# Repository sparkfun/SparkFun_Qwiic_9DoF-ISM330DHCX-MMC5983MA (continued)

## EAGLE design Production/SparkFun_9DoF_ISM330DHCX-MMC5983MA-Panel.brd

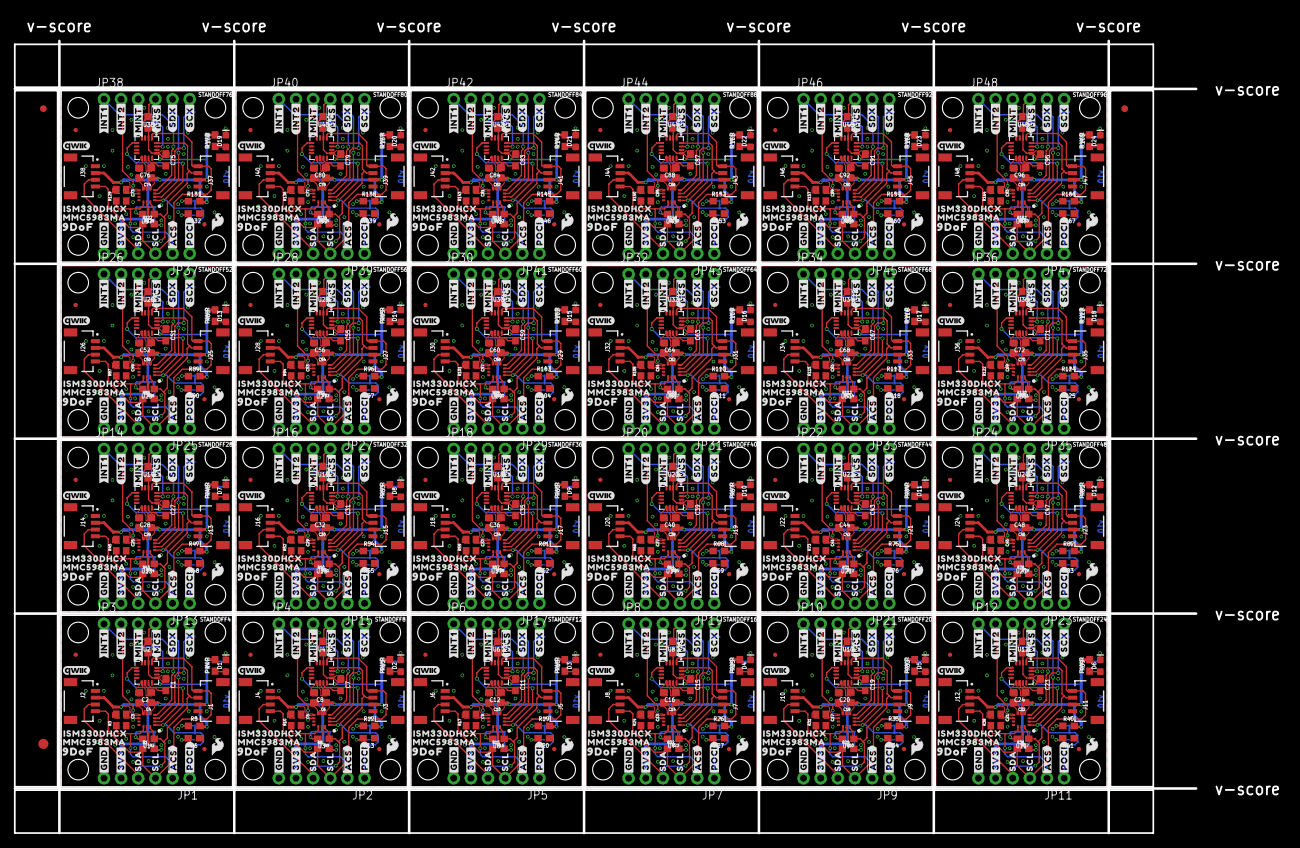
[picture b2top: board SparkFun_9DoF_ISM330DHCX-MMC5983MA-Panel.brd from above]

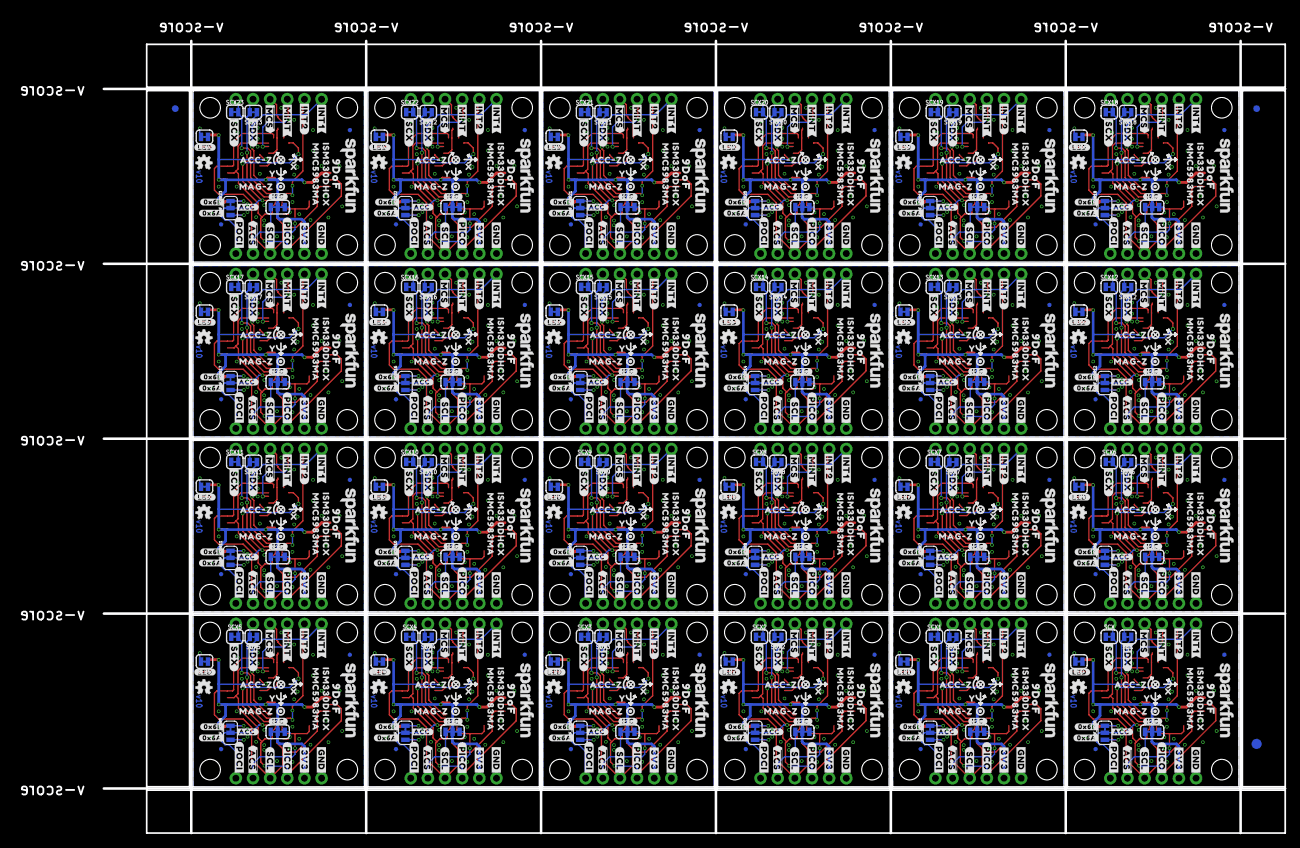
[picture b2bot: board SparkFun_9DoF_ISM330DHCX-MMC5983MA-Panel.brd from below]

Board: 2 copper layers, 175.0 x 117.3 mm, 1806 parts (795 on the bottom side), 456 nets.

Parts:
6DOF_ADDR, 6DOF_ADDR1, 6DOF_ADDR2, 6DOF_ADDR3, 6DOF_ADDR4, 6DOF_ADDR5, 6DOF_ADDR6, 6DOF_ADDR7, 6DOF_ADDR8, 6DOF_ADDR9, 6DOF_ADDR10, 6DOF_ADDR11, 6DOF_ADDR12, 6DOF_ADDR13, 6DOF_ADDR14, 6DOF_ADDR15, 6DOF_ADDR16, 6DOF_ADDR17, 6DOF_ADDR18, 6DOF_ADDR19, 6DOF_ADDR20, 6DOF_ADDR21, 6DOF_ADDR22, 6DOF_ADDR23: JUMPER-SMT_3_1-NC_TRACE_SILK; SMT-JUMPER_3_1-NC_TRACE_SILK
C1, C7, C11, C15, C19, C23, C27, C31, C35, C39, C43, C47, C51, C55, C59, C63, C67, C71, C75, C79, C83, C87, C91, C95: 1.0uF; 0603
C2, C8, C12, C16, C20, C24, C28, C32, C36, C40, C44, C48, C52, C56, C60, C64, C68, C72, C76, C80, C84, C88, C92, C96: 10uF; 0603
C3, C4, C5, C6, C9, C10, C13, C14, C17, C18, C21, C22, C25, C26, C29, C30, C33, C34, C37, C38, C41, C42, C45, C46, C49, C50, C53, C54, C57, C58, C61, C62, C65, C66, C69, C70, C73, C74, C77, C78, C81, C82, C85, C86, C89, C90, C93, C94: 0.1uF; 0603
D1, D2, D3, D4, D5, D6, D7, D8, D9, D10, D11, D12, D13, D14, D15, D16, D17, D18, D19, D20, D21, D22, D23, D24: RED; LED-0603
E$1, E$2, E$3, E$4: FIDUCIAL-1X2
E$5, E$6: FIDUCIAL-1.5X3
FD1, FD2, FD3, FD4, FD5, FD6, FD7, FD8, FD9, FD10, FD11, FD12, FD13, FD14, FD15, FD16, FD17, FD18, FD19, FD20, FD21, FD22, FD23, FD24, FD25, FD26, FD27, FD28, FD29, FD30, FD31, FD32, FD33, FD34, FD35, FD36, FD37, FD38, FD39, FD40, FD41, FD42, FD43, FD44, FD45, FD46, FD47, FD48: FIDUCIALUFIDUCIAL; FIDUCIAL-MICRO
FID1, FID2, FID3, FID4, FID5, FID6, FID7, FID8, FID9, FID10, FID11, FID12, FID13, FID14, FID15, FID16, FID17, FID18, FID19, FID20, FID21, FID22, FID23, FID24, FID25, FID26, FID27, FID28, FID29, FID30, FID31, FID32, FID33, FID34, FID35, FID36, FID37, FID38, FID39, FID40, FID41, FID42, FID43, FID44, FID45, FID46, FID47, FID48: FIDUCIALUFIDUCIAL; FIDUCIAL-MICRO
I2C_PU, I2C_PU1, I2C_PU2, I2C_PU3, I2C_PU4, I2C_PU5, I2C_PU6, I2C_PU7, I2C_PU8, I2C_PU9, I2C_PU10, I2C_PU11, I2C_PU12, I2C_PU13, I2C_PU14, I2C_PU15, I2C_PU16, I2C_PU17, I2C_PU18, I2C_PU19, I2C_PU20, I2C_PU21, I2C_PU22, I2C_PU23: S_MODE; SMT-JUMPER_3_2-NC_TRACE_SILK
J1, J2, J3, J4, J5, J6, J7, J8, J9, J10, J11, J12, J13, J14, J15, J16, J17, J18, J19, J20, J21, J22, J23, J24, J25, J26, J27, J28, J29, J30, J31, J32, J33, J34, J35, J36, J37, J38, J39, J40, J41, J42, J43, J44, J45, J46, J47, J48: QWIIC_RIGHT_ANGLE; JST04_1MM_RA
JP1, JP2, JP3, JP4, JP5, JP6, JP7, JP8, JP9, JP10, JP11, JP12, JP13, JP14, JP15, JP16, JP17, JP18, JP19, JP20, JP21, JP22, JP23, JP24, JP25, JP26, JP27, JP28, JP29, JP30, JP31, JP32, JP33, JP34, JP35, JP36, JP37, JP38, JP39, JP40, JP41, JP42, JP43, JP44, JP45, JP46, JP47, JP48: IO; 1X06_NO_SILK
LED, LED1, LED2, LED3, LED4, LED5, LED6, LED7, LED8, LED9, LED10, LED11, LED12, LED13, LED14, LED15, LED16, LED17, LED18, LED19, LED20, LED21, LED22, LED23: JUMPER-SMT_2_NC_TRACE_SILK; SMT-JUMPER_2_NC_TRACE_SILK
LOGO1, LOGO6, LOGO9, LOGO12, LOGO15, LOGO18, LOGO21, LOGO24, LOGO27, LOGO30, LOGO33, LOGO36, LOGO39, LOGO42, LOGO45, LOGO48, LOGO51, LOGO54, LOGO57, LOGO60, LOGO63, LOGO66, LOGO69, LOGO72: QWIIC_LOGO_4MM; QWIIC_4MM
LOGO2, LOGO4, LOGO7, LOGO10, LOGO13, LOGO16, LOGO19, LOGO22, LOGO25, LOGO28, LOGO31, LOGO34, LOGO37, LOGO40, LOGO43, LOGO46, LOGO49, LOGO52, LOGO55, LOGO58, LOGO61, LOGO64, LOGO67, LOGO70: OSHW-LOGOMINI; OSHW-LOGO-MINI
LOGO3, LOGO5, LOGO8, LOGO11, LOGO14, LOGO17, LOGO20, LOGO23, LOGO26, LOGO29, LOGO32, LOGO35, LOGO38, LOGO41, LOGO44, LOGO47, LOGO50, LOGO53, LOGO56, LOGO59, LOGO62, LOGO65, LOGO68, LOGO71: SFE_LOGO_NAME.1_INCH; SFE_LOGO_NAME_.1
R1, R2, R8, R9, R15, R16, R22, R23, R29, R30, R36, R37, R43, R44, R50, R51, R57, R58, R64, R65, R71, R72, R78, R79, R85, R86, R92, R93, R99, R100, R106, R107, R113, R114, R120, R121, R127, R128, R134, R135, R141, R142, R148, R149, R155, R156, R162, R163: 2.2k; 0603
R3, R5, R6, R7, R10, R12, R13, R14, R17, R19, R20, R21, R24, R26, R27, R28, R31, R33, R34, R35, R38, R40, R41, R42, R45, R47, R48, R49, R52, R54, R55, R56, R59, R61, R62, R63, R66, R68, R69, R70, R73, R75, R76, R77, R80, R82, R83, R84, R87, R89, R90, R91, R94, R96, R97, R98, R101, R103, R104, R105, R108, R110, R111, R112, R115, R117, R118, R119, R122, R124, R125, R126, R129, R131, R132, R133, R136, R138, R139, R140, R143, R145, R146, R147, R150, R152, R153, R154, R157, R159, R160, R161, R164, R166, R167, R168: 100k; 0603
R4, R11, R18, R25, R32, R39, R46, R53, R60, R67, R74, R81, R88, R95, R102, R109, R116, R123, R130, R137, R144, R151, R158, R165: 1k; 0603
SCX, SCX1, SCX2, SCX3, SCX4, SCX5, SCX6, SCX7, SCX8, SCX9, SCX10, SCX11, SCX12, SCX13, SCX14, SCX15, SCX16, SCX17, SCX18, SCX19, SCX20, SCX21, SCX22, SCX23: JUMPER-SMT_2_NC_TRACE_SILK; SMT-JUMPER_2_NC_TRACE_SILK
SDX, SDX1, SDX2, SDX3, SDX4, SDX5, SDX6, SDX7, SDX8, SDX9, SDX10, SDX11, SDX12, SDX13, SDX14, SDX15, SDX16, SDX17, SDX18, SDX19, SDX20, SDX21, SDX22, SDX23: JUMPER-SMT_2_NC_TRACE_SILK; SMT-JUMPER_2_NC_TRACE_SILK
STANDOFF1, STANDOFF2, STANDOFF3, STANDOFF4, STANDOFF5, STANDOFF6, STANDOFF7, STANDOFF8, STANDOFF9, STANDOFF10, STANDOFF11, STANDOFF12, STANDOFF13, STANDOFF14, STANDOFF15, STANDOFF16, STANDOFF17, STANDOFF18, STANDOFF19, STANDOFF20, STANDOFF21, STANDOFF22, STANDOFF23, STANDOFF24, STANDOFF25, STANDOFF26, STANDOFF27, STANDOFF28, STANDOFF29, STANDOFF30, STANDOFF31, STANDOFF32, STANDOFF33, STANDOFF34, STANDOFF35, STANDOFF36, STANDOFF37, STANDOFF38, STANDOFF39, STANDOFF40, STANDOFF41, STANDOFF42, STANDOFF43, STANDOFF44, STANDOFF45, STANDOFF46, STANDOFF47, STANDOFF48, STANDOFF49, STANDOFF50, STANDOFF51, STANDOFF52, STANDOFF53, STANDOFF54, STANDOFF55, STANDOFF56, STANDOFF57, STANDOFF58, STANDOFF59, STANDOFF60, STANDOFF61, STANDOFF62, STANDOFF63, STANDOFF64, STANDOFF65, STANDOFF66, STANDOFF67, STANDOFF68, STANDOFF69, STANDOFF70, STANDOFF71, STANDOFF72, STANDOFF73, STANDOFF74, STANDOFF75, STANDOFF76, STANDOFF77, STANDOFF78, STANDOFF79, STANDOFF80, STANDOFF81, STANDOFF82, STANDOFF83, STANDOFF84, STANDOFF85, STANDOFF86, STANDOFF87, STANDOFF88, STANDOFF89, STANDOFF90, STANDOFF91, STANDOFF92, STANDOFF93, STANDOFF94, STANDOFF95, STANDOFF96: STAND-OFFTIGHT; STAND-OFF-TIGHT
U1, U3, U5, U7, U9, U11, U13, U15, U17, U19, U21, U23, U25, U27, U29, U31, U33, U35, U37, U39, U41, U43, U45, U47: ISM330DHCX; LGA-14L
U2, U4, U6, U8, U10, U12, U14, U16, U18, U20, U22, U24, U26, U28, U30, U32, U34, U36, U38, U40, U42, U44, U46, U48: MMC5983MA_QFN16; LGA-16-3X3MM-4X4PINS
U$1, U$15, U$42, U$44, U$83, U$85, U$124, U$126, U$165, U$167, U$206, U$208, U$247, U$249, U$288, U$290, U$329, U$331, U$370, U$372, U$411, U$413, U$452, U$454, U$493, U$495, U$534, U$536, U$575, U$577, U$616, U$618, U$657, U$659, U$698, U$700, U$739, U$741, U$780, U$782, U$821, U$823, U$862, U$864, U$903, U$905, U$944, U$946: #3V3#1
U$2, U$17, U$43, U$45, U$84, U$86, U$125, U$127, U$166, U$168, U$207, U$209, U$248, U$250, U$289, U$291, U$330, U$332, U$371, U$373, U$412, U$414, U$453, U$455, U$494, U$496, U$535, U$537, U$576, U$578, U$617, U$619, U$658, U$660, U$699, U$701, U$740, U$742, U$781, U$783, U$822, U$824, U$863, U$865, U$904, U$906, U$945, U$947: #GND#0
U$3, U$7, U$64, U$65, U$105, U$106, U$146, U$147, U$187, U$188, U$228, U$229, U$269, U$270, U$310, U$311, U$351, U$352, U$392, U$393, U$433, U$434, U$474, U$475, U$515, U$516, U$556, U$557, U$597, U$598, U$638, U$639, U$679, U$680, U$720, U$721, U$761, U$762, U$802, U$803, U$843, U$844, U$884, U$885, U$925, U$926, U$966, U$967: ISM330DHCX331
U$4, U$78, U$119, U$160, U$201, U$242, U$283, U$324, U$365, U$406, U$447, U$488, U$529, U$570, U$611, U$652, U$693, U$734, U$775, U$816, U$857, U$898, U$939, U$980: SDA14
U$5, U$79, U$120, U$161, U$202, U$243, U$284, U$325, U$366, U$407, U$448, U$489, U$530, U$571, U$612, U$653, U$694, U$735, U$776, U$817, U$858, U$899, U$940, U$981: SCL13
U$6, U$52, U$93, U$134, U$175, U$216, U$257, U$298, U$339, U$380, U$421, U$462, U$503, U$544, U$585, U$626, U$667, U$708, U$749, U$790, U$831, U$872, U$913, U$954: #POCI#11
U$8, U$66, U$107, U$148, U$189, U$230, U$271, U$312, U$353, U$394, U$435, U$476, U$517, U$558, U$599, U$640, U$681, U$722, U$763, U$804, U$845, U$886, U$927, U$968: #INT1#0
U$9, U$74, U$115, U$156, U$197, U$238, U$279, U$320, U$361, U$402, U$443, U$484, U$525, U$566, U$607, U$648, U$689, U$730, U$771, U$812, U$853, U$894, U$935, U$976: #INT2#3
U$10, U$67, U$108, U$149, U$190, U$231, U$272, U$313, U$354, U$395, U$436, U$477, U$518, U$559, U$600, U$641, U$682, U$723, U$764, U$805, U$846, U$887, U$928, U$969: #INT1#2
U$11, U$68, U$109, U$150, U$191, U$232, U$273, U$314, U$355, U$396, U$437, U$478, U$519, U$560, U$601, U$642, U$683, U$724, U$765, U$806, U$847, U$888, U$929, U$970: #INT2#2
U$12, U$69, U$110, U$151, U$192, U$233, U$274, U$315, U$356, U$397, U$438, U$479, U$520, U$561, U$602, U$643, U$684, U$725, U$766, U$807, U$848, U$889, U$930, U$971: #MINT#4
U$13, U$62, U$103, U$144, U$185, U$226, U$267, U$308, U$349, U$390, U$431, U$472, U$513, U$554, U$595, U$636, U$677, U$718, U$759, U$800, U$841, U$882, U$923, U$964: ACC#Z5985
U$14, U$63, U$104, U$145, U$186, U$227, U$268, U$309, U$350, U$391, U$432, U$473, U$514, U$555, U$596, U$637, U$678, U$719, U$760, U$801, U$842, U$883, U$924, U$965: MAG#Z5984
U$16, U$47, U$88, U$129, U$170, U$211, U$252, U$293, U$334, U$375, U$416, U$457, U$498, U$539, U$580, U$621, U$662, U$703, U$744, U$785, U$826, U$867, U$908, U$949: #LED#11
U$18, U$53, U$94, U$135, U$176, U$217, U$258, U$299, U$340, U$381, U$422, U$463, U$504, U$545, U$586, U$627, U$668, U$709, U$750, U$791, U$832, U$873, U$914, U$955: #POCI#12
U$19, U$70, U$111, U$152, U$193, U$234, U$275, U$316, U$357, U$398, U$439, U$480, U$521, U$562, U$603, U$644, U$685, U$726, U$767, U$808, U$849, U$890, U$931, U$972: ##MCS##5
U$20, U$71, U$112, U$153, U$194, U$235, U$276, U$317, U$358, U$399, U$440, U$481, U$522, U$563, U$604, U$645, U$686, U$727, U$768, U$809, U$850, U$891, U$932, U$973: #SDX#7
U$21, U$32, U$56, U$59, U$97, U$100, U$138, U$141, U$179, U$182, U$220, U$223, U$261, U$264, U$302, U$305, U$343, U$346, U$384, U$387, U$425, U$428, U$466, U$469, U$507, U$510, U$548, U$551, U$589, U$592, U$630, U$633, U$671, U$674, U$712, U$715, U$753, U$756, U$794, U$797, U$835, U$838, U$876, U$879, U$917, U$920, U$958, U$961: MMC5983MA24
U$22, U$46, U$87, U$128, U$169, U$210, U$251, U$292, U$333, U$374, U$415, U$456, U$497, U$538, U$579, U$620, U$661, U$702, U$743, U$784, U$825, U$866, U$907, U$948: #SCL#5
U$23, U$72, U$113, U$154, U$195, U$236, U$277, U$318, U$359, U$400, U$441, U$482, U$523, U$564, U$605, U$646, U$687, U$728, U$769, U$810, U$851, U$892, U$933, U$974: #SCX#8
U$24, U$30, U$57, U$58, U$98, U$99, U$139, U$140, U$180, U$181, U$221, U$222, U$262, U$263, U$303, U$304, U$344, U$345, U$385, U$386, U$426, U$427, U$467, U$468, U$508, U$509, U$549, U$550, U$590, U$591, U$631, U$632, U$672, U$673, U$713, U$714, U$754, U$755, U$795, U$796, U$836, U$837, U$877, U$878, U$918, U$919, U$959, U$960: 9DOF24
U$25, U$48, U$89, U$130, U$171, U$212, U$253, U$294, U$335, U$376, U$417, U$458, U$499, U$540, U$581, U$622, U$663, U$704, U$745, U$786, U$827, U$868, U$909, U$950: #I2C#11
U$26, U$51, U$92, U$133, U$174, U$215, U$256, U$297, U$338, U$379, U$420, U$461, U$502, U$543, U$584, U$625, U$666, U$707, U$748, U$789, U$830, U$871, U$912, U$953: #PICO#13
U$27, U$73, U$114, U$155, U$196, U$237, U$278, U$319, U$360, U$401, U$442, U$483, U$524, U$565, U$606, U$647, U$688, U$729, U$770, U$811, U$852, U$893, U$934, U$975: ##ACS##6
U$28, U$49, U$90, U$131, U$172, U$213, U$254, U$295, U$336, U$377, U$418, U$459, U$500, U$541, U$582, U$623, U$664, U$705, U$746, U$787, U$828, U$869, U$910, U$951: PWR8
U$29, U$50, U$91, U$132, U$173, U$214, U$255, U$296, U$337, U$378, U$419, U$460, U$501, U$542, U$583, U$624, U$665, U$706, U$747, U$788, U$829, U$870, U$911, U$952: SFE_LOGO_FLAME_.1
U$31, U$80, U$121, U$162, U$203, U$244, U$285, U$326, U$367, U$408, U$449, U$490, U$531, U$572, U$613, U$654, U$695, U$736, U$777, U$818, U$859, U$900, U$941, U$982: #MINT#5
U$33, U$60, U$101, U$142, U$183, U$224, U$265, U$306, U$347, U$388, U$429, U$470, U$511, U$552, U$593, U$634, U$675, U$716, U$757, U$798, U$839, U$880, U$921, U$962: #0X6A#15
U$34, U$81, U$122, U$163, U$204, U$245, U$286, U$327, U$368, U$409, U$450, U$491, U$532, U$573, U$614, U$655, U$696, U$737, U$778, U$819, U$860, U$901, U$942, U$983: ##MCS##7
U$35, U$75, U$116, U$157, U$198, U$239, U$280, U$321, U$362, U$403, U$444, U$485, U$526, U$567, U$608, U$649, U$690, U$731, U$772, U$813, U$854, U$895, U$936, U$977: #SDX#9
U$36, U$76, U$117, U$158, U$199, U$240, U$281, U$322, U$363, U$404, U$445, U$486, U$527, U$568, U$609, U$650, U$691, U$732, U$773, U$814, U$855, U$896, U$937, U$978: #SCX#11
U$37, U$54, U$95, U$136, U$177, U$218, U$259, U$300, U$341, U$382, U$423, U$464, U$505, U$546, U$587, U$628, U$669, U$710, U$751, U$792, U$833, U$874, U$915, U$956: X2114
U$38, U$55, U$96, U$137, U$178, U$219, U$260, U$301, U$342, U$383, U$424, U$465, U$506, U$547, U$588, U$629, U$670, U$711, U$752, U$793, U$834, U$875, U$916, U$957: Y2115
U$39, U$77, U$118, U$159, U$200, U$241, U$282, U$323, U$364, U$405, U$446, U$487, U$528, U$569, U$610, U$651, U$692, U$733, U$774, U$815, U$856, U$897, U$938, U$979: ##ACS##8
U$40, U$61, U$102, U$143, U$184, U$225, U$266, U$307, U$348, U$389, U$430, U$471, U$512, U$553, U$594, U$635, U$676, U$717, U$758, U$799, U$840, U$881, U$922, U$963: #0X6B#15
U$41, U$82, U$123, U$164, U$205, U$246, U$287, U$328, U$369, U$410, U$451, U$492, U$533, U$574, U$615, U$656, U$697, U$738, U$779, U$820, U$861, U$902, U$943, U$984: #ACC#17

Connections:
3.3V: C1.1, C3.1, C4.1, I2C_PU.2, J1.2, J2.2, JP1.5, R3.2, R4.2, R5.2, R7.2, U1.P5, U1.P8, U2.2, U2.13
3.3V1: C5.1, C6.1, C7.1, I2C_PU1.2, J3.2, J4.2, JP2.5, R10.2, R11.2, R12.2, R14.2, U3.P5, U3.P8, U4.2, U4.13
3.3V2: C9.1, C10.1, C11.1, I2C_PU2.2, J5.2, J6.2, JP5.5, R17.2, R18.2, R19.2, R21.2, U5.P5, U5.P8, U6.2, U6.13
3.3V3: C13.1, C14.1, C15.1, I2C_PU3.2, J7.2, J8.2, JP7.5, R24.2, R25.2, R26.2, R28.2, U7.P5, U7.P8, U8.2, U8.13
3.3V4: C17.1, C18.1, C19.1, I2C_PU4.2, J9.2, J10.2, JP9.5, R31.2, R32.2, R33.2, R35.2, U9.P5, U9.P8, U10.2, U10.13
3.3V5: C21.1, C22.1, C23.1, I2C_PU5.2, J11.2, J12.2, JP11.5, R38.2, R39.2, R40.2, R42.2, U11.P5, U11.P8, U12.2, U12.13
3.3V6: C25.1, C26.1, C27.1, I2C_PU6.2, J13.2, J14.2, JP13.5, R45.2, R46.2, R47.2, R49.2, U13.P5, U13.P8, U14.2, U14.13
3.3V7: C29.1, C30.1, C31.1, I2C_PU7.2, J15.2, J16.2, JP15.5, R52.2, R53.2, R54.2, R56.2, U15.P5, U15.P8, U16.2, U16.13
3.3V8: C33.1, C34.1, C35.1, I2C_PU8.2, J17.2, J18.2, JP17.5, R59.2, R60.2, R61.2, R63.2, U17.P5, U17.P8, U18.2, U18.13
3.3V9: C37.1, C38.1, C39.1, I2C_PU9.2, J19.2, J20.2, JP19.5, R66.2, R67.2, R68.2, R70.2, U19.P5, U19.P8, U20.2, U20.13
3.3V10: C41.1, C42.1, C43.1, I2C_PU10.2, J21.2, J22.2, JP21.5, R73.2, R74.2, R75.2, R77.2, U21.P5, U21.P8, U22.2, U22.13
3.3V11: C45.1, C46.1, C47.1, I2C_PU11.2, J23.2, J24.2, JP23.5, R80.2, R81.2, R82.2, R84.2, U23.P5, U23.P8, U24.2, U24.13
3.3V12: C49.1, C50.1, C51.1, I2C_PU12.2, J25.2, J26.2, JP25.5, R87.2, R88.2, R89.2, R91.2, U25.P5, U25.P8, U26.2, U26.13
3.3V13: C53.1, C54.1, C55.1, I2C_PU13.2, J27.2, J28.2, JP27.5, R94.2, R95.2, R96.2, R98.2, U27.P5, U27.P8, U28.2, U28.13
3.3V14: C57.1, C58.1, C59.1, I2C_PU14.2, J29.2, J30.2, JP29.5, R101.2, R102.2, R103.2, R105.2, U29.P5, U29.P8, U30.2, U30.13
3.3V15: C61.1, C62.1, C63.1, I2C_PU15.2, J31.2, J32.2, JP31.5, R108.2, R109.2, R110.2, R112.2, U31.P5, U31.P8, U32.2, U32.13
3.3V16: C65.1, C66.1, C67.1, I2C_PU16.2, J33.2, J34.2, JP33.5, R115.2, R116.2, R117.2, R119.2, U33.P5, U33.P8, U34.2, U34.13
3.3V17: C69.1, C70.1, C71.1, I2C_PU17.2, J35.2, J36.2, JP35.5, R122.2, R123.2, R124.2, R126.2, U35.P5, U35.P8, U36.2, U36.13
3.3V18: C73.1, C74.1, C75.1, I2C_PU18.2, J37.2, J38.2, JP37.5, R129.2, R130.2, R131.2, R133.2, U37.P5, U37.P8, U38.2, U38.13
3.3V19: C77.1, C78.1, C79.1, I2C_PU19.2, J39.2, J40.2, JP39.5, R136.2, R137.2, R138.2, R140.2, U39.P5, U39.P8, U40.2, U40.13
3.3V20: C81.1, C82.1, C83.1, I2C_PU20.2, J41.2, J42.2, JP41.5, R143.2, R144.2, R145.2, R147.2, U41.P5, U41.P8, U42.2, U42.13
3.3V21: C85.1, C86.1, C87.1, I2C_PU21.2, J43.2, J44.2, JP43.5, R150.2, R151.2, R152.2, R154.2, U43.P5, U43.P8, U44.2, U44.13
3.3V22: C89.1, C90.1, C91.1, I2C_PU22.2, J45.2, J46.2, JP45.5, R157.2, R158.2, R159.2, R161.2, U45.P5, U45.P8, U46.2, U46.13
3.3V23: C93.1, C94.1, C95.1, I2C_PU23.2, J47.2, J48.2, JP47.5, R164.2, R165.2, R166.2, R168.2, U47.P5, U47.P8, U48.2, U48.13
!ISM_CS!: JP1.2, R3.1, U1.P12
!ISM_CS!1: JP2.2, R10.1, U3.P12
!ISM_CS!2: JP5.2, R17.1, U5.P12
!ISM_CS!3: JP7.2, R24.1, U7.P12
!ISM_CS!4: JP9.2, R31.1, U9.P12
!ISM_CS!5: JP11.2, R38.1, U11.P12
!ISM_CS!6: JP13.2, R45.1, U13.P12
!ISM_CS!7: JP15.2, R52.1, U15.P12
!ISM_CS!8: JP17.2, R59.1, U17.P12
!ISM_CS!9: JP19.2, R66.1, U19.P12
!ISM_CS!10: JP21.2, R73.1, U21.P12
!ISM_CS!11: JP23.2, R80.1, U23.P12
!ISM_CS!12: JP25.2, R87.1, U25.P12
!ISM_CS!13: JP27.2, R94.1, U27.P12
!ISM_CS!14: JP29.2, R101.1, U29.P12
!ISM_CS!15: JP31.2, R108.1, U31.P12
!ISM_CS!16: JP33.2, R115.1, U33.P12
!ISM_CS!17: JP35.2, R122.1, U35.P12
!ISM_CS!18: JP37.2, R129.1, U37.P12
!ISM_CS!19: JP39.2, R136.1, U39.P12
!ISM_CS!20: JP41.2, R143.1, U41.P12
!ISM_CS!21: JP43.2, R150.1, U43.P12
!ISM_CS!22: JP45.2, R157.1, U45.P12
!ISM_CS!23: JP47.2, R164.1, U47.P12
!MAG_CS!: JP3.4, R7.1, U2.4
!MAG_CS!1: JP4.4, R14.1, U4.4
!MAG_CS!2: JP6.4, R21.1, U6.4
!MAG_CS!3: JP8.4, R28.1, U8.4
!MAG_CS!4: JP10.4, R35.1, U10.4
!MAG_CS!5: JP12.4, R42.1, U12.4
!MAG_CS!6: JP14.4, R49.1, U14.4
!MAG_CS!7: JP16.4, R56.1, U16.4
!MAG_CS!8: JP18.4, R63.1, U18.4
!MAG_CS!9: JP20.4, R70.1, U20.4
!MAG_CS!10: JP22.4, R77.1, U22.4
!MAG_CS!11: JP24.4, R84.1, U24.4
!MAG_CS!12: JP26.4, R91.1, U26.4
!MAG_CS!13: JP28.4, R98.1, U28.4
!MAG_CS!14: JP30.4, R105.1, U30.4
!MAG_CS!15: JP32.4, R112.1, U32.4
!MAG_CS!16: JP34.4, R119.1, U34.4
!MAG_CS!17: JP36.4, R126.1, U36.4
!MAG_CS!18: JP38.4, R133.1, U38.4
!MAG_CS!19: JP40.4, R140.1, U40.4
!MAG_CS!20: JP42.4, R147.1, U42.4
!MAG_CS!21: JP44.4, R154.1, U44.4
!MAG_CS!22: JP46.4, R161.1, U46.4
!MAG_CS!23: JP48.4, R168.1, U48.4
CAP: C2.1, U2.10
CAP1: C8.1, U4.10
CAP2: C12.1, U6.10
CAP3: C16.1, U8.10
CAP4: C20.1, U10.10
CAP5: C24.1, U12.10
CAP6: C28.1, U14.10
CAP7: C32.1, U16.10
CAP8: C36.1, U18.10
CAP9: C40.1, U20.10
CAP10: C44.1, U22.10
CAP11: C48.1, U24.10
CAP12: C52.1, U26.10
CAP13: C56.1, U28.10
CAP14: C60.1, U30.10
CAP15: C64.1, U32.10
CAP16: C68.1, U34.10
CAP17: C72.1, U36.10
CAP18: C76.1, U38.10
CAP19: C80.1, U40.10
CAP20: C84.1, U42.10
CAP21: C88.1, U44.10
CAP22: C92.1, U46.10
CAP23: C96.1, U48.10
GND: C1.2, C2.2, C3.2, C4.2, J1.1, J2.1, JP1.6, LED.1, R6.1, SCX.1, SDX.1, U1.P6, U1.P7, U2.9, U2.11
GND1: C5.2, C6.2, C7.2, C8.2, J3.1, J4.1, JP2.6, LED1.1, R13.1, SCX1.1, SDX1.1, U3.P6, U3.P7, U4.9, U4.11
GND2: C9.2, C10.2, C11.2, C12.2, J5.1, J6.1, JP5.6, LED2.1, R20.1, SCX2.1, SDX2.1, U5.P6, U5.P7, U6.9, U6.11
GND3: C13.2, C14.2, C15.2, C16.2, J7.1, J8.1, JP7.6, LED3.1, R27.1, SCX3.1, SDX3.1, U7.P6, U7.P7, U8.9, U8.11
GND4: C17.2, C18.2, C19.2, C20.2, J9.1, J10.1, JP9.6, LED4.1, R34.1, SCX4.1, SDX4.1, U9.P6, U9.P7, U10.9, U10.11
GND5: C21.2, C22.2, C23.2, C24.2, J11.1, J12.1, JP11.6, LED5.1, R41.1, SCX5.1, SDX5.1, U11.P6, U11.P7, U12.9, U12.11
GND6: C25.2, C26.2, C27.2, C28.2, J13.1, J14.1, JP13.6, LED6.1, R48.1, SCX6.1, SDX6.1, U13.P6, U13.P7, U14.9, U14.11
GND7: C29.2, C30.2, C31.2, C32.2, J15.1, J16.1, JP15.6, LED7.1, R55.1, SCX7.1, SDX7.1, U15.P6, U15.P7, U16.9, U16.11
GND8: C33.2, C34.2, C35.2, C36.2, J17.1, J18.1, JP17.6, LED8.1, R62.1, SCX8.1, SDX8.1, U17.P6, U17.P7, U18.9, U18.11
GND9: C37.2, C38.2, C39.2, C40.2, J19.1, J20.1, JP19.6, LED9.1, R69.1, SCX9.1, SDX9.1, U19.P6, U19.P7, U20.9, U20.11
GND10: C41.2, C42.2, C43.2, C44.2, J21.1, J22.1, JP21.6, LED10.1, R76.1, SCX10.1, SDX10.1, U21.P6, U21.P7, U22.9, U22.11
GND11: C45.2, C46.2, C47.2, C48.2, J23.1, J24.1, JP23.6, LED11.1, R83.1, SCX11.1, SDX11.1, U23.P6, U23.P7, U24.9, U24.11
GND12: C49.2, C50.2, C51.2, C52.2, J25.1, J26.1, JP25.6, LED12.1, R90.1, SCX12.1, SDX12.1, U25.P6, U25.P7, U26.9, U26.11
GND13: C53.2, C54.2, C55.2, C56.2, J27.1, J28.1, JP27.6, LED13.1, R97.1, SCX13.1, SDX13.1, U27.P6, U27.P7, U28.9, U28.11
GND14: C57.2, C58.2, C59.2, C60.2, J29.1, J30.1, JP29.6, LED14.1, R104.1, SCX14.1, SDX14.1, U29.P6, U29.P7, U30.9, U30.11
GND15: C61.2, C62.2, C63.2, C64.2, J31.1, J32.1, JP31.6, LED15.1, R111.1, SCX15.1, SDX15.1, U31.P6, U31.P7, U32.9, U32.11
GND16: C65.2, C66.2, C67.2, C68.2, J33.1, J34.1, JP33.6, LED16.1, R118.1, SCX16.1, SDX16.1, U33.P6, U33.P7, U34.9, U34.11
GND17: C69.2, C70.2, C71.2, C72.2, J35.1, J36.1, JP35.6, LED17.1, R125.1, SCX17.1, SDX17.1, U35.P6, U35.P7, U36.9, U36.11
GND18: C73.2, C74.2, C75.2, C76.2, J37.1, J38.1, JP37.6, LED18.1, R132.1, SCX18.1, SDX18.1, U37.P6, U37.P7, U38.9, U38.11
GND19: C77.2, C78.2, C79.2, C80.2, J39.1, J40.1, JP39.6, LED19.1, R139.1, SCX19.1, SDX19.1, U39.P6, U39.P7, U40.9, U40.11
GND20: C81.2, C82.2, C83.2, C84.2, J41.1, J42.1, JP41.6, LED20.1, R146.1, SCX20.1, SDX20.1, U41.P6, U41.P7, U42.9, U42.11
GND21: C85.2, C86.2, C87.2, C88.2, J43.1, J44.1, JP43.6, LED21.1, R153.1, SCX21.1, SDX21.1, U43.P6, U43.P7, U44.9, U44.11
GND22: C89.2, C90.2, C91.2, C92.2, J45.1, J46.1, JP45.6, LED22.1, R160.1, SCX22.1, SDX22.1, U45.P6, U45.P7, U46.9, U46.11
GND23: C93.2, C94.2, C95.2, C96.2, J47.1, J48.1, JP47.6, LED23.1, R167.1, SCX23.1, SDX23.1, U47.P6, U47.P7, U48.9, U48.11
ISM_INT1: JP3.1, U1.P4
ISM_INT2: JP3.2, U1.P9
ISM_INT3: JP4.1, U3.P4
ISM_INT4: JP4.2, U3.P9
ISM_INT5: JP6.1, U5.P4
ISM_INT6: JP6.2, U5.P9
ISM_INT7: JP8.1, U7.P4
ISM_INT8: JP8.2, U7.P9
ISM_INT9: JP10.1, U9.P4
ISM_INT10: JP10.2, U9.P9
ISM_INT11: JP12.1, U11.P4
ISM_INT12: JP12.2, U11.P9
ISM_INT13: JP14.1, U13.P4
ISM_INT14: JP14.2, U13.P9
ISM_INT15: JP16.1, U15.P4
ISM_INT16: JP16.2, U15.P9
ISM_INT17: JP18.1, U17.P4
ISM_INT18: JP18.2, U17.P9
ISM_INT19: JP20.1, U19.P4
ISM_INT20: JP20.2, U19.P9
ISM_INT21: JP22.1, U21.P4
ISM_INT22: JP22.2, U21.P9
ISM_INT23: JP24.1, U23.P4
ISM_INT24: JP24.2, U23.P9
ISM_INT25: JP26.1, U25.P4
ISM_INT26: JP26.2, U25.P9
ISM_INT27: JP28.1, U27.P4
ISM_INT28: JP28.2, U27.P9
ISM_INT29: JP30.1, U29.P4
ISM_INT30: JP30.2, U29.P9
ISM_INT31: JP32.1, U31.P4
ISM_INT32: JP32.2, U31.P9
ISM_INT33: JP34.1, U33.P4
ISM_INT34: JP34.2, U33.P9
ISM_INT35: JP36.1, U35.P4
ISM_INT36: JP36.2, U35.P9
ISM_INT37: JP38.1, U37.P4
ISM_INT38: JP38.2, U37.P9
ISM_INT39: JP40.1, U39.P4
ISM_INT40: JP40.2, U39.P9
ISM_INT41: JP42.1, U41.P4
ISM_INT42: JP42.2, U41.P9
ISM_INT43: JP44.1, U43.P4
ISM_INT44: JP44.2, U43.P9
ISM_INT45: JP46.1, U45.P4
ISM_INT46: JP46.2, U45.P9
ISM_INT47: JP48.1, U47.P4
ISM_INT48: JP48.2, U47.P9
MAG_INT: JP3.3, U2.15
MAG_INT1: JP4.3, U4.15
MAG_INT2: JP6.3, U6.15
MAG_INT3: JP8.3, U8.15
MAG_INT4: JP10.3, U10.15
MAG_INT5: JP12.3, U12.15
MAG_INT6: JP14.3, U14.15
MAG_INT7: JP16.3, U16.15
MAG_INT8: JP18.3, U18.15
MAG_INT9: JP20.3, U20.15
MAG_INT10: JP22.3, U22.15
MAG_INT11: JP24.3, U24.15
MAG_INT12: JP26.3, U26.15
MAG_INT13: JP28.3, U28.15
MAG_INT14: JP30.3, U30.15
MAG_INT15: JP32.3, U32.15
MAG_INT16: JP34.3, U34.15
MAG_INT17: JP36.3, U36.15
MAG_INT18: JP38.3, U38.15
MAG_INT19: JP40.3, U40.15
MAG_INT20: JP42.3, U42.15
MAG_INT21: JP44.3, U44.15
MAG_INT22: JP46.3, U46.15
MAG_INT23: JP48.3, U48.15
unnamed: 6DOF_ADDR.3, R5.1
unnamed: D1.A, R4.1
unnamed: D1.C, LED.2
unnamed: I2C_PU1.1, R8.2
unnamed: I2C_PU.1, R1.2
unnamed: I2C_PU.3, R2.2
unnamed: 6DOF_ADDR.1, R6.2
unnamed: I2C_PU1.3, R9.2
unnamed: D2.A, R11.1
unnamed: D2.C, LED1.2
unnamed: 6DOF_ADDR1.3, R12.1
unnamed: 6DOF_ADDR1.1, R13.2
unnamed: I2C_PU2.1, R15.2
unnamed: I2C_PU2.3, R16.2
unnamed: D3.A, R18.1
unnamed: D3.C, LED2.2
unnamed: 6DOF_ADDR2.3, R19.1
unnamed: 6DOF_ADDR2.1, R20.2
unnamed: I2C_PU3.1, R22.2
unnamed: I2C_PU3.3, R23.2
unnamed: D4.A, R25.1
unnamed: D4.C, LED3.2
unnamed: 6DOF_ADDR3.3, R26.1
unnamed: 6DOF_ADDR3.1, R27.2
unnamed: I2C_PU4.1, R29.2
unnamed: I2C_PU4.3, R30.2
unnamed: D5.A, R32.1
unnamed: D5.C, LED4.2
unnamed: 6DOF_ADDR4.3, R33.1
unnamed: 6DOF_ADDR4.1, R34.2
unnamed: I2C_PU5.1, R36.2
unnamed: I2C_PU5.3, R37.2
unnamed: D6.A, R39.1
unnamed: D6.C, LED5.2
unnamed: 6DOF_ADDR5.3, R40.1
unnamed: 6DOF_ADDR5.1, R41.2
unnamed: I2C_PU6.1, R43.2
unnamed: I2C_PU6.3, R44.2
unnamed: D7.A, R46.1
unnamed: D7.C, LED6.2
unnamed: 6DOF_ADDR6.3, R47.1
unnamed: 6DOF_ADDR6.1, R48.2
unnamed: I2C_PU7.1, R50.2
unnamed: I2C_PU7.3, R51.2
unnamed: D8.A, R53.1
unnamed: D8.C, LED7.2
unnamed: 6DOF_ADDR7.3, R54.1
unnamed: 6DOF_ADDR7.1, R55.2
unnamed: I2C_PU8.1, R57.2
unnamed: I2C_PU8.3, R58.2
unnamed: D9.A, R60.1
unnamed: D9.C, LED8.2
unnamed: 6DOF_ADDR8.3, R61.1
unnamed: 6DOF_ADDR8.1, R62.2
unnamed: I2C_PU9.1, R64.2
unnamed: I2C_PU9.3, R65.2
unnamed: D10.A, R67.1
unnamed: D10.C, LED9.2
unnamed: 6DOF_ADDR9.3, R68.1
unnamed: 6DOF_ADDR9.1, R69.2
unnamed: I2C_PU10.1, R71.2
unnamed: I2C_PU10.3, R72.2
unnamed: D11.A, R74.1
unnamed: D11.C, LED10.2
unnamed: 6DOF_ADDR10.3, R75.1
unnamed: 6DOF_ADDR10.1, R76.2
unnamed: I2C_PU11.1, R78.2
unnamed: I2C_PU11.3, R79.2
unnamed: D12.A, R81.1
unnamed: D12.C, LED11.2
unnamed: 6DOF_ADDR11.3, R82.1
unnamed: 6DOF_ADDR11.1, R83.2
unnamed: I2C_PU12.1, R85.2
unnamed: I2C_PU12.3, R86.2
unnamed: D13.A, R88.1
unnamed: D13.C, LED12.2
unnamed: 6DOF_ADDR12.3, R89.1
unnamed: 6DOF_ADDR12.1, R90.2
unnamed: I2C_PU13.1, R92.2
unnamed: I2C_PU13.3, R93.2
unnamed: D14.A, R95.1
unnamed: D14.C, LED13.2
unnamed: 6DOF_ADDR13.3, R96.1
unnamed: 6DOF_ADDR13.1, R97.2
unnamed: I2C_PU14.1, R99.2
unnamed: I2C_PU14.3, R100.2
unnamed: D15.A, R102.1
unnamed: D15.C, LED14.2
unnamed: 6DOF_ADDR14.3, R103.1
unnamed: 6DOF_ADDR14.1, R104.2
unnamed: I2C_PU15.1, R106.2
unnamed: I2C_PU15.3, R107.2
unnamed: D16.A, R109.1
unnamed: D16.C, LED15.2
unnamed: 6DOF_ADDR15.3, R110.1
unnamed: 6DOF_ADDR15.1, R111.2
unnamed: I2C_PU16.1, R113.2
unnamed: I2C_PU16.3, R114.2
unnamed: D17.A, R116.1
unnamed: D17.C, LED16.2
unnamed: 6DOF_ADDR16.3, R117.1
unnamed: 6DOF_ADDR16.1, R118.2
unnamed: I2C_PU17.1, R120.2
unnamed: I2C_PU17.3, R121.2
unnamed: D18.A, R123.1
unnamed: D18.C, LED17.2
unnamed: 6DOF_ADDR17.3, R124.1
unnamed: 6DOF_ADDR17.1, R125.2
unnamed: I2C_PU18.1, R127.2
unnamed: I2C_PU18.3, R128.2
unnamed: D19.A, R130.1
unnamed: D19.C, LED18.2
unnamed: 6DOF_ADDR18.3, R131.1
unnamed: 6DOF_ADDR18.1, R132.2
unnamed: I2C_PU19.1, R134.2
unnamed: I2C_PU19.3, R135.2
unnamed: D20.A, R137.1
unnamed: D20.C, LED19.2
unnamed: 6DOF_ADDR19.3, R138.1
unnamed: 6DOF_ADDR19.1, R139.2
unnamed: I2C_PU20.1, R141.2
unnamed: I2C_PU20.3, R142.2
unnamed: D21.A, R144.1
unnamed: D21.C, LED20.2
unnamed: 6DOF_ADDR20.3, R145.1
unnamed: 6DOF_ADDR20.1, R146.2
unnamed: I2C_PU21.1, R148.2
unnamed: I2C_PU21.3, R149.2
unnamed: D22.A, R151.1
unnamed: D22.C, LED21.2
unnamed: 6DOF_ADDR21.3, R152.1
unnamed: 6DOF_ADDR21.1, R153.2
unnamed: I2C_PU22.1, R155.2
unnamed: I2C_PU22.3, R156.2
unnamed: D23.A, R158.1
unnamed: D23.C, LED22.2
unnamed: 6DOF_ADDR22.3, R159.1
unnamed: 6DOF_ADDR22.1, R160.2
unnamed: I2C_PU23.1, R162.2
unnamed: I2C_PU23.3, R163.2
unnamed: D24.A, R165.1
unnamed: D24.C, LED23.2
unnamed: 6DOF_ADDR23.3, R166.1
unnamed: 6DOF_ADDR23.1, R167.2
POCI/SA0: 6DOF_ADDR.2, JP1.1, U1.P1, U2.5
POCI/SA1: 6DOF_ADDR1.2, JP2.1, U3.P1, U4.5
POCI/SA2: 6DOF_ADDR2.2, JP5.1, U5.P1, U6.5
POCI/SA3: 6DOF_ADDR3.2, JP7.1, U7.P1, U8.5
POCI/SA4: 6DOF_ADDR4.2, JP9.1, U9.P1, U10.5
POCI/SA5: 6DOF_ADDR5.2, JP11.1, U11.P1, U12.5
POCI/SA6: 6DOF_ADDR6.2, JP13.1, U13.P1, U14.5
POCI/SA7: 6DOF_ADDR7.2, JP15.1, U15.P1, U16.5
POCI/SA8: 6DOF_ADDR8.2, JP17.1, U17.P1, U18.5
POCI/SA9: 6DOF_ADDR9.2, JP19.1, U19.P1, U20.5
POCI/SA10: 6DOF_ADDR10.2, JP21.1, U21.P1, U22.5
POCI/SA11: 6DOF_ADDR11.2, JP23.1, U23.P1, U24.5
POCI/SA12: 6DOF_ADDR12.2, JP25.1, U25.P1, U26.5
POCI/SA13: 6DOF_ADDR13.2, JP27.1, U27.P1, U28.5
POCI/SA14: 6DOF_ADDR14.2, JP29.1, U29.P1, U30.5
POCI/SA15: 6DOF_ADDR15.2, JP31.1, U31.P1, U32.5
POCI/SA16: 6DOF_ADDR16.2, JP33.1, U33.P1, U34.5
POCI/SA17: 6DOF_ADDR17.2, JP35.1, U35.P1, U36.5
POCI/SA18: 6DOF_ADDR18.2, JP37.1, U37.P1, U38.5
POCI/SA19: 6DOF_ADDR19.2, JP39.1, U39.P1, U40.5
POCI/SA20: 6DOF_ADDR20.2, JP41.1, U41.P1, U42.5
POCI/SA21: 6DOF_ADDR21.2, JP43.1, U43.P1, U44.5
POCI/SA22: 6DOF_ADDR22.2, JP45.1, U45.P1, U46.5
POCI/SA23: 6DOF_ADDR23.2, JP47.1, U47.P1, U48.5
SCL/SCK: J1.4, J2.4, JP1.3, R1.1, U1.P13, U2.1
SCL/SCK1: J3.4, J4.4, JP2.3, R8.1, U3.P13, U4.1
SCL/SCK2: J5.4, J6.4, JP5.3, R15.1, U5.P13, U6.1
SCL/SCK3: J7.4, J8.4, JP7.3, R22.1, U7.P13, U8.1
SCL/SCK4: J9.4, J10.4, JP9.3, R29.1, U9.P13, U10.1
SCL/SCK5: J11.4, J12.4, JP11.3, R36.1, U11.P13, U12.1
SCL/SCK6: J13.4, J14.4, JP13.3, R43.1, U13.P13, U14.1
SCL/SCK7: J15.4, J16.4, JP15.3, R50.1, U15.P13, U16.1
SCL/SCK8: J17.4, J18.4, JP17.3, R57.1, U17.P13, U18.1
SCL/SCK9: J19.4, J20.4, JP19.3, R64.1, U19.P13, U20.1
SCL/SCK10: J21.4, J22.4, JP21.3, R71.1, U21.P13, U22.1
SCL/SCK11: J23.4, J24.4, JP23.3, R78.1, U23.P13, U24.1
SCL/SCK12: J25.4, J26.4, JP25.3, R85.1, U25.P13, U26.1
SCL/SCK13: J27.4, J28.4, JP27.3, R92.1, U27.P13, U28.1
SCL/SCK14: J29.4, J30.4, JP29.3, R99.1, U29.P13, U30.1
SCL/SCK15: J31.4, J32.4, JP31.3, R106.1, U31.P13, U32.1
SCL/SCK16: J33.4, J34.4, JP33.3, R113.1, U33.P13, U34.1
SCL/SCK17: J35.4, J36.4, JP35.3, R120.1, U35.P13, U36.1
SCL/SCK18: J37.4, J38.4, JP37.3, R127.1, U37.P13, U38.1
SCL/SCK19: J39.4, J40.4, JP39.3, R134.1, U39.P13, U40.1
SCL/SCK20: J41.4, J42.4, JP41.3, R141.1, U41.P13, U42.1
SCL/SCK21: J43.4, J44.4, JP43.3, R148.1, U43.P13, U44.1
SCL/SCK22: J45.4, J46.4, JP45.3, R155.1, U45.P13, U46.1
SCL/SCK23: J47.4, J48.4, JP47.3, R162.1, U47.P13, U48.1
SCX: JP3.6, SCX.2, U1.P3
SCX1: JP4.6, SCX1.2, U3.P3
SCX2: JP6.6, SCX2.2, U5.P3
SCX3: JP8.6, SCX3.2, U7.P3
SCX4: JP10.6, SCX4.2, U9.P3
SCX5: JP12.6, SCX5.2, U11.P3
SCX6: JP14.6, SCX6.2, U13.P3
SCX7: JP16.6, SCX7.2, U15.P3
SCX8: JP18.6, SCX8.2, U17.P3
SCX9: JP20.6, SCX9.2, U19.P3
SCX10: JP22.6, SCX10.2, U21.P3
SCX11: JP24.6, SCX11.2, U23.P3
SCX12: JP26.6, SCX12.2, U25.P3
SCX13: JP28.6, SCX13.2, U27.P3
SCX14: JP30.6, SCX14.2, U29.P3
SCX15: JP32.6, SCX15.2, U31.P3
SCX16: JP34.6, SCX16.2, U33.P3
SCX17: JP36.6, SCX17.2, U35.P3
SCX18: JP38.6, SCX18.2, U37.P3
SCX19: JP40.6, SCX19.2, U39.P3
SCX20: JP42.6, SCX20.2, U41.P3
SCX21: JP44.6, SCX21.2, U43.P3
SCX22: JP46.6, SCX22.2, U45.P3
SCX23: JP48.6, SCX23.2, U47.P3
SDA/PICO: J1.3, J2.3, JP1.4, R2.1, U1.P14, U2.16
SDA/PICO1: J3.3, J4.3, JP2.4, R9.1, U3.P14, U4.16
SDA/PICO2: J5.3, J6.3, JP5.4, R16.1, U5.P14, U6.16
SDA/PICO3: J7.3, J8.3, JP7.4, R23.1, U7.P14, U8.16
SDA/PICO4: J9.3, J10.3, JP9.4, R30.1, U9.P14, U10.16
SDA/PICO5: J11.3, J12.3, JP11.4, R37.1, U11.P14, U12.16
SDA/PICO6: J13.3, J14.3, JP13.4, R44.1, U13.P14, U14.16
SDA/PICO7: J15.3, J16.3, JP15.4, R51.1, U15.P14, U16.16
SDA/PICO8: J17.3, J18.3, JP17.4, R58.1, U17.P14, U18.16
SDA/PICO9: J19.3, J20.3, JP19.4, R65.1, U19.P14, U20.16
SDA/PICO10: J21.3, J22.3, JP21.4, R72.1, U21.P14, U22.16
SDA/PICO11: J23.3, J24.3, JP23.4, R79.1, U23.P14, U24.16
SDA/PICO12: J25.3, J26.3, JP25.4, R86.1, U25.P14, U26.16
SDA/PICO13: J27.3, J28.3, JP27.4, R93.1, U27.P14, U28.16
SDA/PICO14: J29.3, J30.3, JP29.4, R100.1, U29.P14, U30.16
SDA/PICO15: J31.3, J32.3, JP31.4, R107.1, U31.P14, U32.16
SDA/PICO16: J33.3, J34.3, JP33.4, R114.1, U33.P14, U34.16
SDA/PICO17: J35.3, J36.3, JP35.4, R121.1, U35.P14, U36.16
SDA/PICO18: J37.3, J38.3, JP37.4, R128.1, U37.P14, U38.16
SDA/PICO19: J39.3, J40.3, JP39.4, R135.1, U39.P14, U40.16
SDA/PICO20: J41.3, J42.3, JP41.4, R142.1, U41.P14, U42.16
SDA/PICO21: J43.3, J44.3, JP43.4, R149.1, U43.P14, U44.16
SDA/PICO22: J45.3, J46.3, JP45.4, R156.1, U45.P14, U46.16
SDA/PICO23: J47.3, J48.3, JP47.4, R163.1, U47.P14, U48.16
SDX: JP3.5, SDX.2, U1.P2
SDX1: JP4.5, SDX1.2, U3.P2
SDX2: JP6.5, SDX2.2, U5.P2
SDX3: JP8.5, SDX3.2, U7.P2
SDX4: JP10.5, SDX4.2, U9.P2
SDX5: JP12.5, SDX5.2, U11.P2
SDX6: JP14.5, SDX6.2, U13.P2
SDX7: JP16.5, SDX7.2, U15.P2
SDX8: JP18.5, SDX8.2, U17.P2
SDX9: JP20.5, SDX9.2, U19.P2
SDX10: JP22.5, SDX10.2, U21.P2
SDX11: JP24.5, SDX11.2, U23.P2
SDX12: JP26.5, SDX12.2, U25.P2
SDX13: JP28.5, SDX13.2, U27.P2
SDX14: JP30.5, SDX14.2, U29.P2
SDX15: JP32.5, SDX15.2, U31.P2
SDX16: JP34.5, SDX16.2, U33.P2
SDX17: JP36.5, SDX17.2, U35.P2
SDX18: JP38.5, SDX18.2, U37.P2
SDX19: JP40.5, SDX19.2, U39.P2
SDX20: JP42.5, SDX20.2, U41.P2
SDX21: JP44.5, SDX21.2, U43.P2
SDX22: JP46.5, SDX22.2, U45.P2
SDX23: JP48.5, SDX23.2, U47.P2
